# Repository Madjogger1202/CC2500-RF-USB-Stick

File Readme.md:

# CC2500-RF-USB-Stick  

> USB RF transceiver stick based on **CC2500RGPR** and **FT4222H** (USB↔SPI bridge).  
> Implemented as a **USB flash-drive style dongle** with on-board PCB antenna.  

---

## What’s on the board  
- **FT4222H USB-SPI bridge**  
  - Provides standard SPI master interface over USB  
  - Enumerates as USB device (driver support in Windows/Linux)  
- **CC2500RGPR RF transceiver**  
  - Sub-1 GHz / 2.4 GHz ISM band  
  - Connected directly to FT4222H SPI  
  - Standard configuration mode supported  
- **PCB antenna** integrated into board  
- **USB 2.0 Type-A plug** (flash-stick style)  
- Power from USB bus only (no external supply)  

---

## Pinout (FT4222H ↔ CC2500)  

| FT4222H Pin | CC2500 Pin | Notes |
|-------------|------------|-------|
| SCLK | SCLK | SPI clock |
| MOSI | SI   | SPI data out |
| MISO | SO   | SPI data in |
| CS0  | CSn  | Chip select |
| X | GDO0/GDO2 | Interrupt / status lines |

---

## Power & Form Factor  
- Powered directly from **USB Type-A**  
- Compact PCB with integrated RF antenna  
- No extra components required to operate  

---

## Use Case  
- RF packet capture and transmission via **CC2500**  
- USB plug-and-play stick for wireless experiments  
- Can be used in custom RF tools, sniffers, IoT gateways  

---

## Quick Use  
1. Plug **CC2500-RF-USB-Stick** into USB port.  
2. Install FT4222H driver (if required).  
3. Use SPI commands over FT4222H to configure and control CC2500.  
4. Transmit/receive RF packets in 2.4 GHz band.  

---

## Notes  
- PCB antenna may require tuning for optimal performance.  
- CC2500 settings (frequency, modulation, packet format) configurable via SPI.  
- Heat dissipation negligible (low-power device).  

---

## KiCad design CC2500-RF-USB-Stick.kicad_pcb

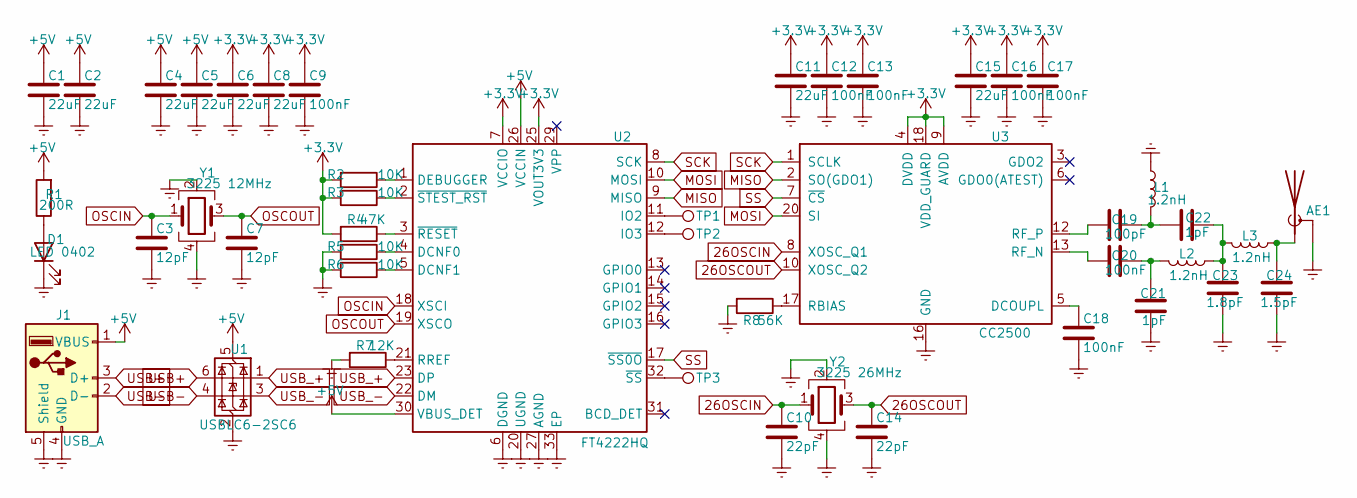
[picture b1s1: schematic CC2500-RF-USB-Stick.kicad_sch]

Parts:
AE1: Antenna_Shield; Texas_SWRA117D_2.4GHz_Right
C1, C2, C4, C5, C6, C8, C11, C15: 22uF; C_0402_1005Metric
C3, C7: 12pF; C_0402_1005Metric
C9, C12, C13, C16, C17, C18, C20: 100nF; C_0402_1005Metric
C10, C14: 22pF; C_0402_1005Metric
C19: 100pF; C_0402_1005Metric
C21, C22: 1pF; C_0402_1005Metric
C23: 1.8pF; C_0402_1005Metric
C24: 1.5pF; C_0402_1005Metric
D1: LED 0402; LED_0402_1005Metric
J1: USB_A; USB_A_CNCTech_1001-011-01101_Horizontal
L1, L2, L3: 1.2nH; L_0402_1005Metric
R1: 200R; R_0402_1005Metric
R2, R3, R5, R6: 10K; R_0402_1005Metric
R4: 47K; R_0402_1005Metric
R7: 12K; R_0402_1005Metric
R8: 56K; R_0402_1005Metric
TP1, TP2, TP3: TestPoint; TestPoint_Pad_D1.0mm
U1: USBLC6-2SC6; SOT-23-6
U2: FT4222HQ; VQFN-32-1EP_5x5mm_P0.5mm_EP3.1x3.1mm
U3: CC2500; Texas_RGP0020H_VQFN-20-1EP_4x4mm_P0.5mm_EP2.4x2.4mm
Y1: 3225 12MHz; Crystal_SMD_3225-4Pin_3.2x2.5mm
Y2: 3225 26MHz; Crystal_SMD_3225-4Pin_3.2x2.5mm

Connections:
26OSCIN: C10.1, U3.8 (XOSC_Q1), Y2.1
26OSCOUT: C14.1, U3.10 (XOSC_Q2), Y2.3
+3.3V: C6.1, C8.1, C9.1, C11.1, C12.1, C13.1, C15.1, C16.1, C17.1, R2.2, R3.2, R4.2, U2.7 (VCCIO), U2.25 (VOUT3V3), U3.4 (DVDD), U3.9 (AVDD), U3.11 (AVDD), U3.14 (AVDD), U3.15 (AVDD), U3.18 (VDD_GUARD)
+5V: C1.1, C2.1, C4.1, C5.1, J1.1 (VBUS), R1.2, U1.5 (VBUS), U2.26 (VCCIN), U2.30 (VBUS_DET)
Earth: AE1.2 (Shield), C1.2, C2.2, C3.2, C4.2, C5.2, C6.2, C7.2, C8.2, C9.2, C10.2, C11.2, C12.2, C13.2, C14.2, C15.2, C16.2, C17.2, C18.2, C21.1, C23.1, C24.1, D1.1 (K), J1.4 (GND), J1.5 (Shield), L1.1, R5.2, R6.2, R7.2, R8.2, U1.2 (GND), U2.6 (DGND), U2.20 (UGND), U2.24 (UGND), U2.27 (AGND), U2.28 (DGND), U2.33 (EP), U3.16 (GND), U3.19 (GND), U3.21 (GND), Y1.2, Y1.4, Y2.2, Y2.4
MISO: U2.9 (MISO), U3.2 (SO(GDO1))
MOSI: U2.10 (MOSI), U3.20 (SI)
unnamed: AE1.1 (A), C24.2, L3.1
unnamed: C19.2, C22.1, L1.2
unnamed: C20.2, C21.2, L2.2
unnamed: C22.2, C23.2, L2.1, L3.2
unnamed: D1.2 (A), R1.1
unnamed: R5.1, U2.4 (DCNF0)
unnamed: R6.1, U2.5 (DCNF1)
unnamed: R2.1, U2.1 (DEBUGGER)
unnamed: TP1.1, U2.11 (IO2)
unnamed: TP2.1, U2.12 (IO3)
unnamed: R7.1, U2.21 (RREF)
unnamed: R4.1, U2.3 (~RESET)
unnamed: TP3.1, U2.32 (~SS)
unnamed: R3.1, U2.2 (~STEST_RST)
unnamed: C18.1, U3.5 (DCOUPL)
unnamed: R8.1, U3.17 (RBIAS)
unnamed: C20.1, U3.13 (RF_N)
unnamed: C19.1, U3.12 (RF_P)
OSCIN: C3.1, U2.18 (XSCI), Y1.1
OSCOUT: C7.1, U2.19 (XSCO), Y1.3
SCK: U2.8 (SCK), U3.1 (SCLK)
SS: U2.17 (~SS0O), U3.7 (~CS)
USB+: J1.3 (D+), U1.6 (I/O1)
USB-: J1.2 (D-), U1.4 (I/O2)
USB_+: U1.1 (I/O1), U2.23 (DP)
USB_-: U1.3 (I/O2), U2.22 (DM)

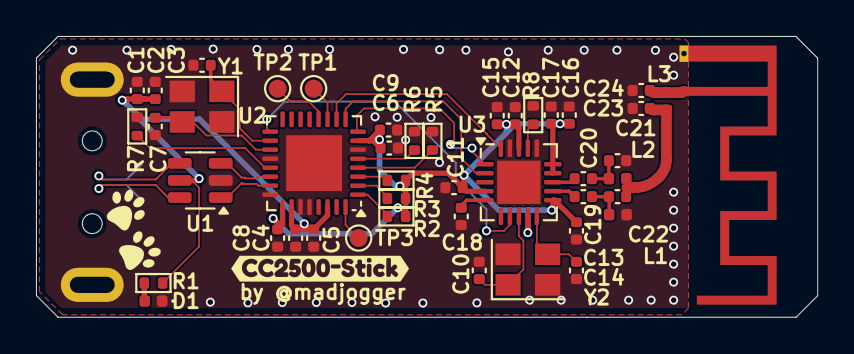
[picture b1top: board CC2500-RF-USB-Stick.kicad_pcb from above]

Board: 2 copper layers, 43.4 x 15.6 mm, 47 parts (1 on the bottom side), 33 nets.

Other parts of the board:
kibuzzard-68B8A8C4: G***; kibuzzard-68B8A8C4

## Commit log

2025-09-03 rev0 ready
